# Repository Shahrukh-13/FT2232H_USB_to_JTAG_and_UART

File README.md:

# FT2232H_USB_to_JTAG_and_UART
Setting up FT2232H as XDS100V2 to work as USB to JTAG and UART adapter to program Texas Instruments Microcontrollers

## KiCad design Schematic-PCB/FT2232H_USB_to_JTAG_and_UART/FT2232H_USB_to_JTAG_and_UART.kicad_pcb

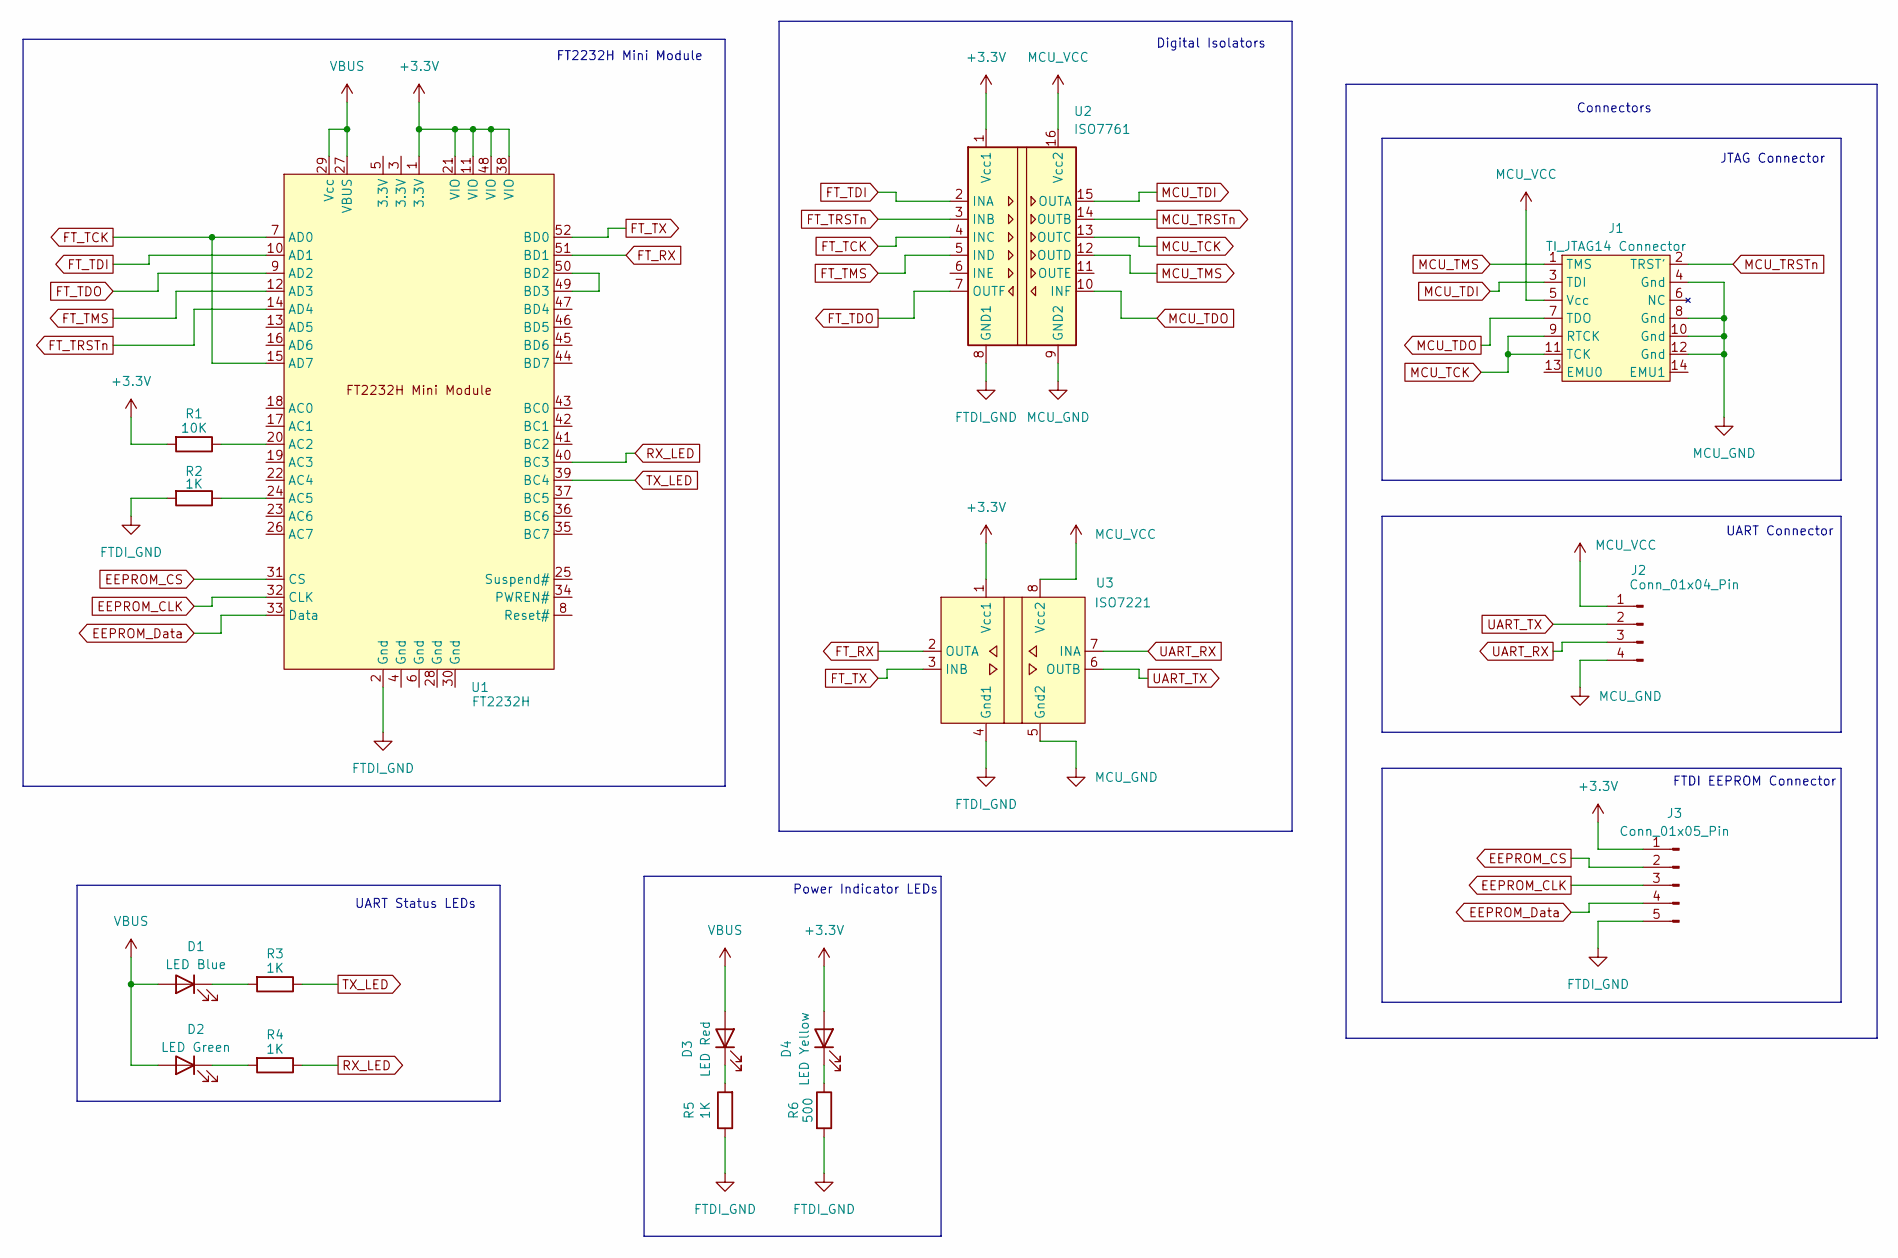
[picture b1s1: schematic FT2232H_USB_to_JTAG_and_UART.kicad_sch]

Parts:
D1: LED Blue; LED_D5.0mm
D2: LED Green; LED_D5.0mm
D3: LED Red; LED_D5.0mm
D4: LED Yellow; LED_D5.0mm
J1: TI_JTAG14 Connector; Connector_TI_JTAG14
J2: Conn_01x04_Pin; PinHeader_1x04_P2.54mm_Vertical
J3: Conn_01x05_Pin; PinHeader_1x05_P2.54mm_Vertical
R1: 10K; R_Axial_DIN0207_L6.3mm_D2.5mm_P10.16mm_Horizontal
R2, R3, R4, R5: 1K; R_Axial_DIN0207_L6.3mm_D2.5mm_P10.16mm_Horizontal
R6: 500; R_Axial_DIN0207_L6.3mm_D2.5mm_P10.16mm_Horizontal
U1: FT2232H; FT2232H_Mini_Module
U2: ISO7761; SOIC_16-DIP
U3: ISO7221; SOIC_8-DIP

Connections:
+3.3V: D4.2 (A), J3.1, R1.2, U1.1 (3.3V), U1.11 (VIO), U1.21 (VIO), U1.38 (VIO), U1.48 (VIO), U2.1 (Vcc1), U3.1 (Vcc1)
EEPROM_CLK: J3.3, U1.32 (CLK)
EEPROM_CS: J3.2, U1.31 (CS)
EEPROM_Data: J3.4, U1.33 (Data)
FTDI_GND: J3.5, R2.2, R5.1, R6.2, U1.2 (Gnd), U2.8 (GND1), U3.4 (Gnd1)
FT_RX: U1.51 (BD1), U3.2 (OUTA)
FT_TCK: U1.7 (AD0), U1.15 (AD7), U2.4 (INC)
FT_TDI: U1.10 (AD1), U2.2 (INA)
FT_TDO: U1.9 (AD2), U2.7 (OUTF)
FT_TMS: U1.12 (AD3), U2.5 (IND)
FT_TRSTn: U1.14 (AD4), U2.3 (INB)
FT_TX: U1.52 (BD0), U3.3 (INB)
MCU_GND: J1.4 (Gnd), J1.8 (Gnd), J1.10 (Gnd), J1.12 (Gnd), J2.4, U2.9 (GND2), U3.5 (Gnd2)
MCU_TCK: J1.9 (RTCK), J1.11 (TCK), U2.13 (OUTC)
MCU_TDI: J1.3 (TDI), U2.15 (OUTA)
MCU_TDO: J1.7 (TDO), U2.10 (INF)
MCU_TMS: J1.1 (TMS), U2.12 (OUTD)
MCU_TRSTn: J1.2 (TRST'), U2.14 (OUTB)
MCU_VCC: J1.5 (Vcc), J2.1, U2.16 (Vcc2), U3.8 (Vcc2)
unnamed: D1.1 (K), R3.2
unnamed: D2.1 (K), R4.2
unnamed: D3.1 (K), R5.2
unnamed: D4.1 (K), R6.1
unnamed: R1.1, U1.20 (AC2)
unnamed: R2.1, U1.24 (AC5)
unnamed: U1.49 (BD3), U1.50 (BD2)
RX_LED: R4.1, U1.40 (BC3)
TX_LED: R3.1, U1.39 (BC4)
UART_RX: J2.3, U3.7 (INA)
UART_TX: J2.2, U3.6 (OUTB)
VBUS: D1.2 (A), D2.2 (A), D3.2 (A), U1.27 (VBUS), U1.29 (Vcc)

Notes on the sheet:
JTAG Connector
UART Connector
FTDI EEPROM Connector
UART Status LEDs
Digital Isolators
FT2232H Mini Module
Connectors
Power Indicator LEDs

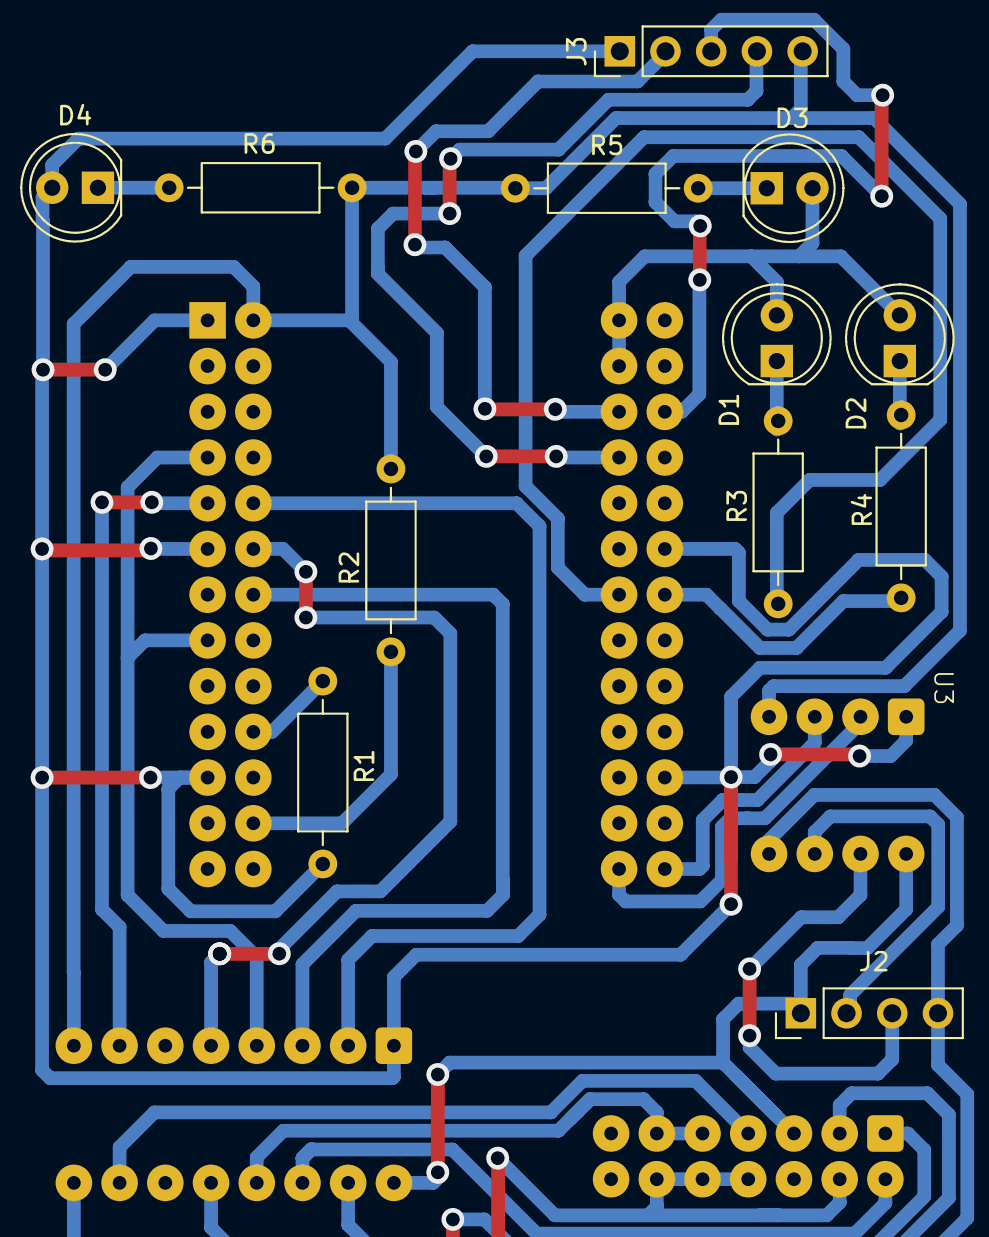
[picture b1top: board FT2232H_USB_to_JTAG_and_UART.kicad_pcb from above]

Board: 2 copper layers, 16 parts (0 on the bottom side), 31 nets.

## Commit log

2025-04-26 Added Kicad project
2025-04-27 Updated Kicad project, added PCB layout PDF files and FT2232H XML file
2025-05-18 Removed buffer IC from schematic
2025-05-18 Changed a resistor value
